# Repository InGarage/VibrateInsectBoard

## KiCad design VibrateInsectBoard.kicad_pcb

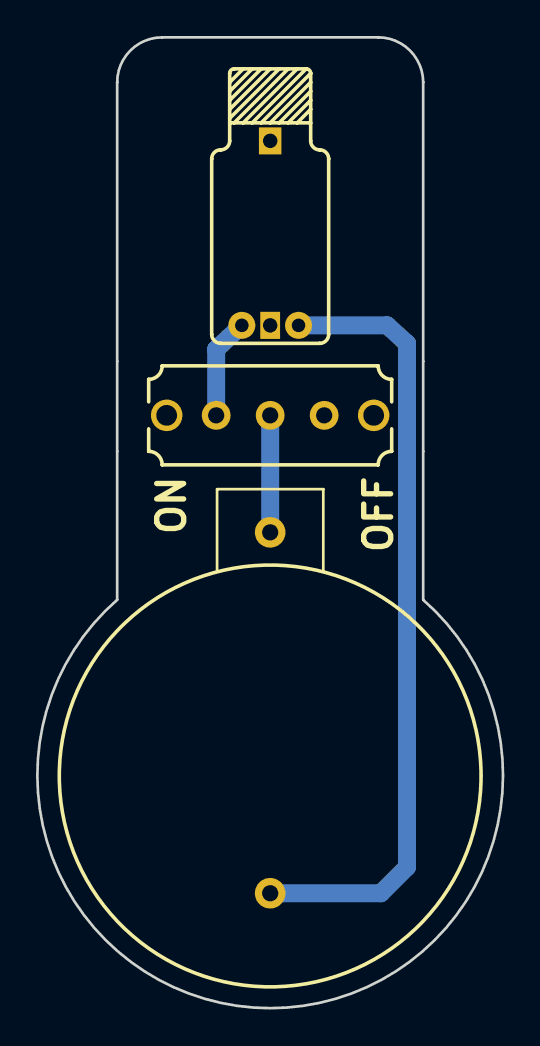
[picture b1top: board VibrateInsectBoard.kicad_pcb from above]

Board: 2 copper layers, 25.9 x 53.9 mm, 3 parts (0 on the bottom side), 3 nets.

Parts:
BT1: CR2032; BL-25T-GLT
M1: Vibrator; VibrationMotor_0601
SW1: SW_SPDT; SS-12F108- G10

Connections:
unnamed: BT1.1, SW1.2
unnamed: BT1.2, M1.2
unnamed: M1.1, SW1.1

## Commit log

2019-09-20 First commit.
2019-09-27 Fix footprint and resize PCB. All done.
